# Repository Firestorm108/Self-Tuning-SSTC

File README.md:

# Self-Tuning-SSTC

A solid state Tesla coil that utilizes a half-bridge configuration, automatic tuning through an antenna so that the coil is always in perfect resonance, and a 555-based interrupter. It runs straight off 120VAC with FGA60N65 IGBTs, allowing it to push many many watts. This should make for a good display at Open Sauce 2026.

# Warning

Please do NOT make this under any circumstances unless you are experienced in the field. While this is a solid state coil, it runs off 340VDC from mains and is lethal to anyone who doesn't know what they are doing. I recommened starting with a simple slayer exciter circuit or low voltage primary SSTC circuits. I do not hold any responsibility for what you choose to do with this information.

Demo: https://www.instagram.com/p/DbAHNh3O-ZV/

## Main Features:

 - Integrated 340VDC and 12VDC power supplies
 - 555 Timer Interrupter
 - Antenna feedback
 - Gate drive transformer
 - Half-bridge
 - FGA60N65 based

## Pictures:

# SSTC BOM
*You can find the spreadsheet version here: https://docs.google.com/spreadsheets/d/1Wt0Rxcv9VSmFwRn_iBSPhIluuYkqVSy19_F0Ip-qjvU/edit?usp=sharing

# Bill of Materials (BOM)

## Components

| Item                         | Price | Source  |
| ---------------------------- | ----: | ------- |
| PCB                          |    $5 | JLCPCB  |
| 1N4007                       | $0.76 | DigiKey |
| 10K Potentiometer            | $3.56 | DigiKey |
| Resistor Kit                 |    $5 | Amazon  |
| 470µF 18V Capacitors (×3)    |    $1 | DigiKey |
| 1N4148                       | $0.40 | DigiKey |
| Ceramic Capacitor Kit        |    $7 | Amazon  |
| Ferrite 77                   |    $2 | DigiKey |
| 1N5818                       | $1.50 | DigiKey |
| FGA60N65                     |   $15 | DigiKey |
| Thermistor (30A / 1Ω)        |   $10 | Amazon  |
| L7805                        |    $6 | Amazon  |
| KBPF307G                     |    $1 | DigiKey |
| 0.82µF / 600V Film Capacitor |   $10 | DigiKey |
| KBPC5010W                    |    $4 | DigiKey |
| 1000µF 250V Capacitors (×2)  |   $15 | DigiKey |
| LM555xN                      | $1.50 | DigiKey |
| LM7812 (TO-220)              | $1.80 | DigiKey |
| Screw Terminals              |    $6 | Amazon  |
| 30AWG Magnet Wire            |   $22 | Amazon  |
| 4.5" × 12" PVC Tube          |   $21 | Amazon  |
| Topload                      |   $20 | eBay    |
| Mains Cord                   |    $6 | Amazon  |
| 15mm M3 Standoffs            |    $8 | Amazon  |
| IEC Power Inlet              |    $9 | Amazon  |
| 12VAC Transformer            |   $14 | Amazon  |
| Antenna                      | Owned |         |
| EMI Shielding Tape           |    $7 | Amazon  |
| Rubber Feet                  | Owned |         |
| TO-220 Heatsinks             |    $8 | Amazon  |
| 12AWG Wire                   |   $12 | Amazon  |
| IRFP460                      |   $10 | Amazon  |

---

## Cost Summary

| Vendor  |    Total |
| ------- | -------: |
| DigiKey |  **$80** |
| Amazon  | **$170** |
| eBay    |  **$22** |

### Total Project Cost: **$272**

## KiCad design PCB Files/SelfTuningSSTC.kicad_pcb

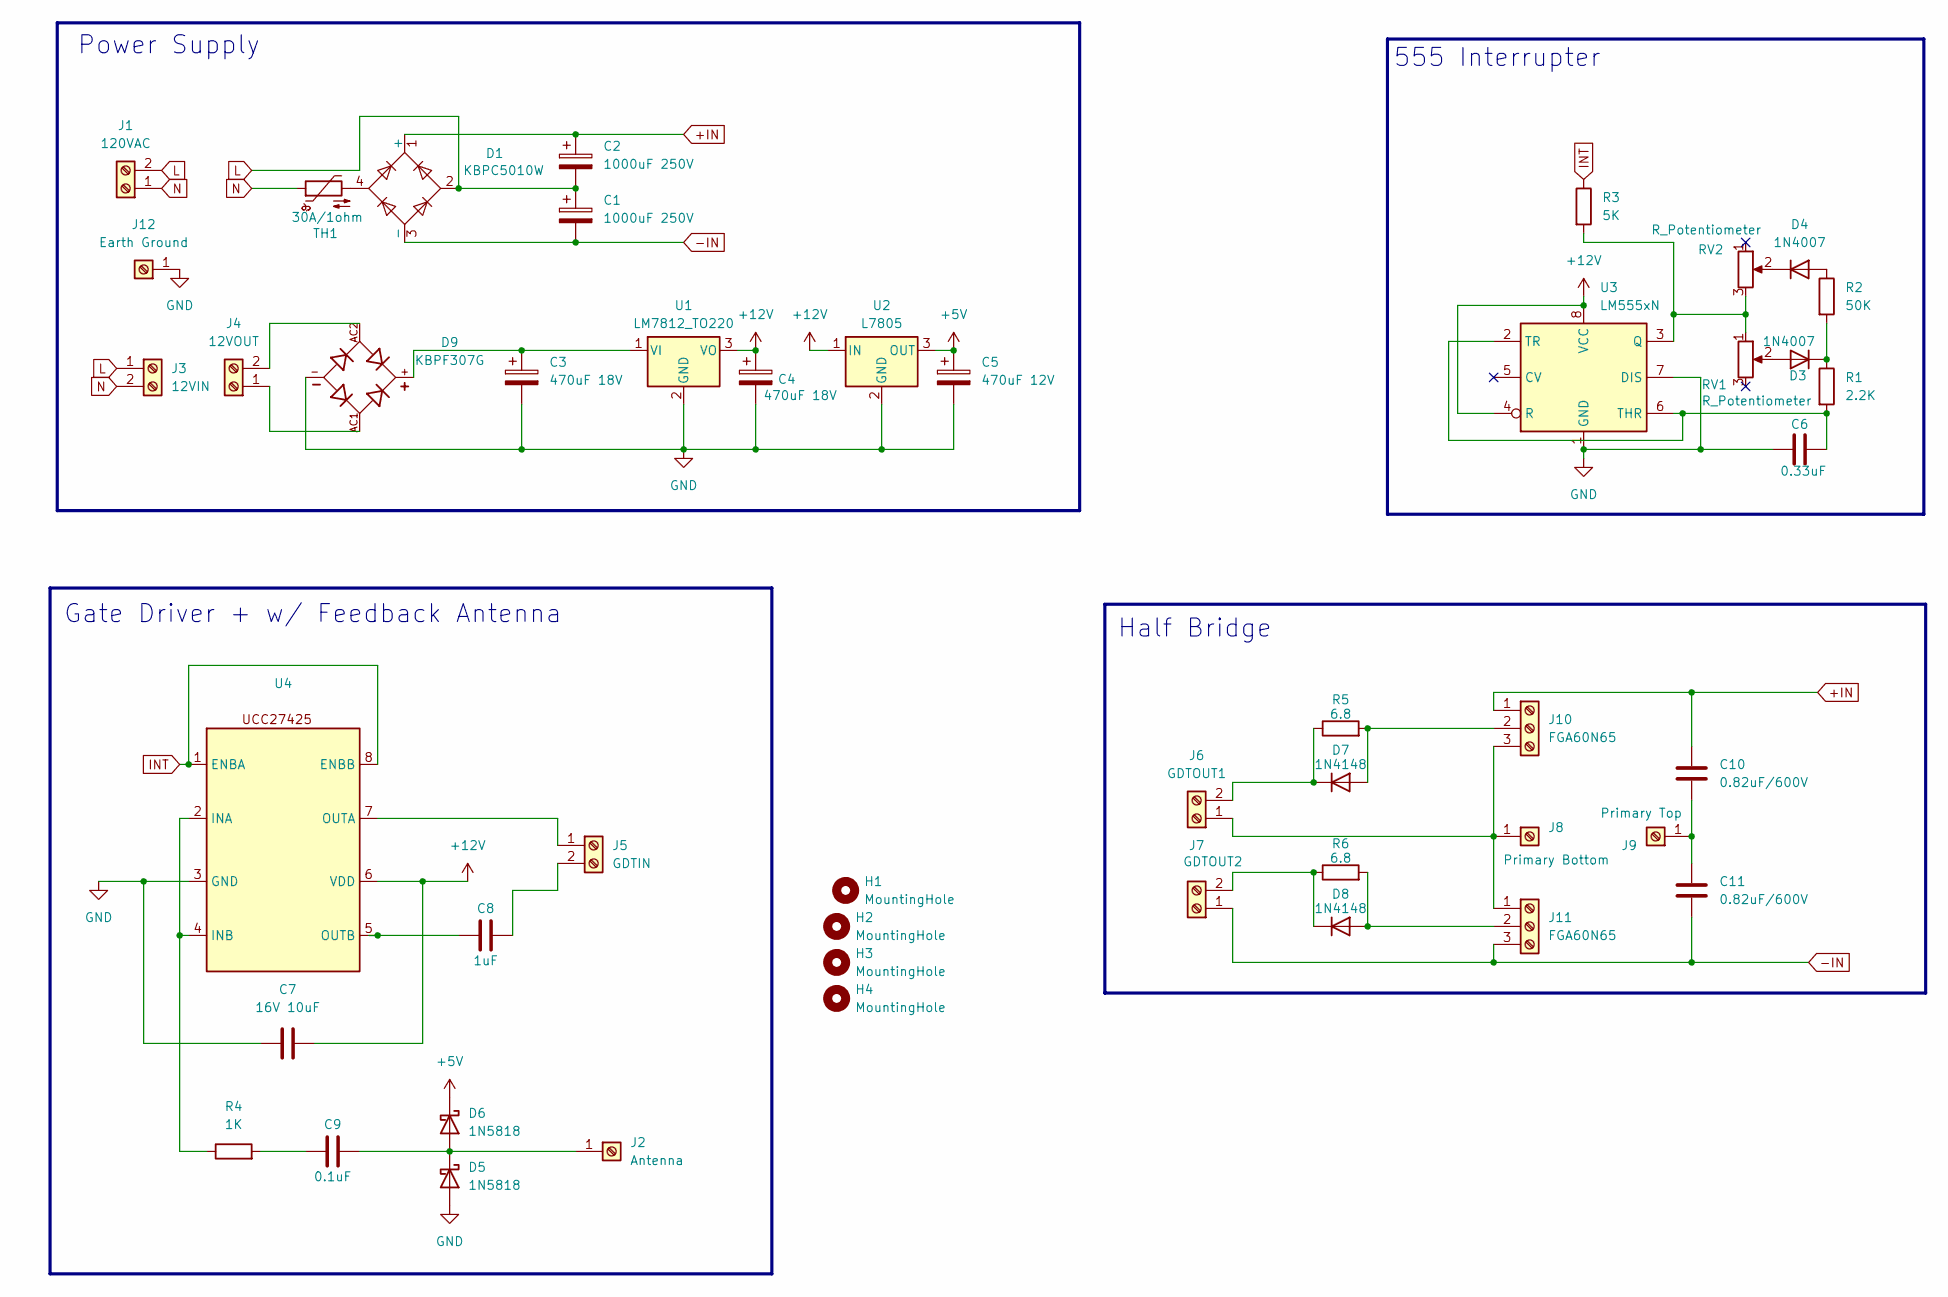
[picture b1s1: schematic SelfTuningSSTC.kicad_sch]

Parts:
C1, C2: 1000uF 250V; CP_Radial_D22.0mm_P10.00mm_SnapIn
C3, C4: 470uF 18V; CP_Radial_D8.0mm_P3.50mm
C5: 470uF 12V; CP_Radial_D8.0mm_P3.50mm
C6: 0.33uF; C_Disc_D5.0mm_W2.5mm_P2.50mm
C7: 16V 10uF; C_Disc_D5.0mm_W2.5mm_P2.50mm
C8: 1uF; C_Disc_D5.0mm_W2.5mm_P2.50mm
C9: 0.1uF; C_Disc_D5.0mm_W2.5mm_P2.50mm
C10, C11: 0.82uF/600V; C_Rect_L31.5mm_W13.0mm_P27.50mm_MKS4
D1: KBPC5010W; Diode_Bridge_GeneSiC_KBPC_W
D3, D4: 1N4007; D_DO-41_SOD81_P10.16mm_Horizontal
D5, D6: 1N5818; D_DO-41_SOD81_P10.16mm_Horizontal
D7, D8: 1N4148; D_DO-35_SOD27_P7.62mm_Horizontal
D9: KBPF307G; SIP350W81P380L1450H1280Q4; PARTREV B2103
H1, H2, H3, H4: MountingHole; MountingHole_3.2mm_M3
J1: 120VAC; PinHeader_1x02_P2.54mm_Vertical
J2: Antenna; PinHeader_1x01_P2.54mm_Vertical
J3: 12VIN; PinHeader_1x02_P2.54mm_Vertical
J4: 12VOUT; PinHeader_1x02_P2.54mm_Vertical
J5: GDTIN; PinHeader_1x02_P2.54mm_Vertical
J6: GDTOUT1; PinHeader_1x02_P2.54mm_Vertical
J7: GDTOUT2; PinHeader_1x02_P2.54mm_Vertical
J8: Primary Bottom; PinHeader_1x01_P2.54mm_Vertical
J9: Primary Top; PinHeader_1x01_P2.54mm_Vertical
J10, J11: FGA60N65; PinHeader_1x03_P2.54mm_Vertical
J12: Earth Ground; PinHeader_1x01_P2.54mm_Vertical
R1: 2.2K; R_Axial_DIN0207_L6.3mm_D2.5mm_P10.16mm_Horizontal
R2: 50K; R_Axial_DIN0207_L6.3mm_D2.5mm_P10.16mm_Horizontal
R3: 5K; R_Axial_DIN0207_L6.3mm_D2.5mm_P10.16mm_Horizontal
R4: 1K; R_Axial_DIN0207_L6.3mm_D2.5mm_P10.16mm_Horizontal
R5, R6: 6.8; R_Axial_DIN0207_L6.3mm_D2.5mm_P10.16mm_Horizontal
RV1, RV2: R_Potentiometer; Potentiometer_Alpha_RD901F-40-00D_Single_Vertical
TH1: 30A/1ohm; RV_Disc_D12mm_W7.9mm_P7.5mm
U1: LM7812_TO220; TO-220-3_Vertical
U2: L7805; TO-220-3_Vertical
U3: LM555xN; DIP-8_W7.62mm
U4: DIP-8_W7.62mm

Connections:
+5V: C5.1, D6.1 (K), U2.3 (OUT)
+12V: C4.1, C7.2, U1.3 (VO), U2.1 (IN), U3.4 (R), U3.8 (VCC), U4.6 (VDD)
+IN: C2.1, C10.1, D1.1 (+), J10.1
-IN: C1.2, C11.2, D1.3 (-), J7.1, J11.3
GND: C3.2, C4.2, C5.2, C6.1, C7.1, D5.2 (A), D9.-, J12.1, U1.2 (GND), U2.2 (GND), U3.1 (GND), U3.7 (DIS), U4.3 (GND)
INT: R3.1, U4.1 (ENBA), U4.8 (ENBB)
L: C1.1, C2.2, D1.2, J1.2, J3.1
N: J1.1, J3.2, TH1.1
unnamed: C9.1, R4.2
unnamed: D1.4, TH1.2
unnamed: D3.2 (A), RV1.2
unnamed: D3.1 (K), R1.1, R2.2
unnamed: D4.2 (A), R2.1
unnamed: D4.1 (K), RV2.2
unnamed: C9.2, D5.1 (K), D6.2 (A), J2.1
unnamed: D7.2 (A), J10.2, R5.2
unnamed: D7.1 (K), J6.2, R5.1
unnamed: D8.2 (A), J11.2, R6.2
unnamed: D8.1 (K), J7.2, R6.1
unnamed: D9.AC1, J4.1
unnamed: D9.AC2, J4.2
unnamed: J5.1, U4.7 (OUTA)
unnamed: C8.2, J5.2
unnamed: C10.2, C11.1, J9.1
unnamed: J6.1, J8.1, J10.3, J11.1
unnamed: C3.1, D9.+, U1.1 (VI)
unnamed: R3.2, RV1.1, RV2.3, U3.3 (Q)
unnamed: C6.2, R1.2, U3.2 (TR), U3.6 (THR)
unnamed: R4.1, U4.2 (INA), U4.4 (INB)
unnamed: C8.1, U4.5 (OUTB)

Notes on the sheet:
Half Bridge
555 Interrupter
Power Supply
Gate Driver + w/ Feedback Antenna

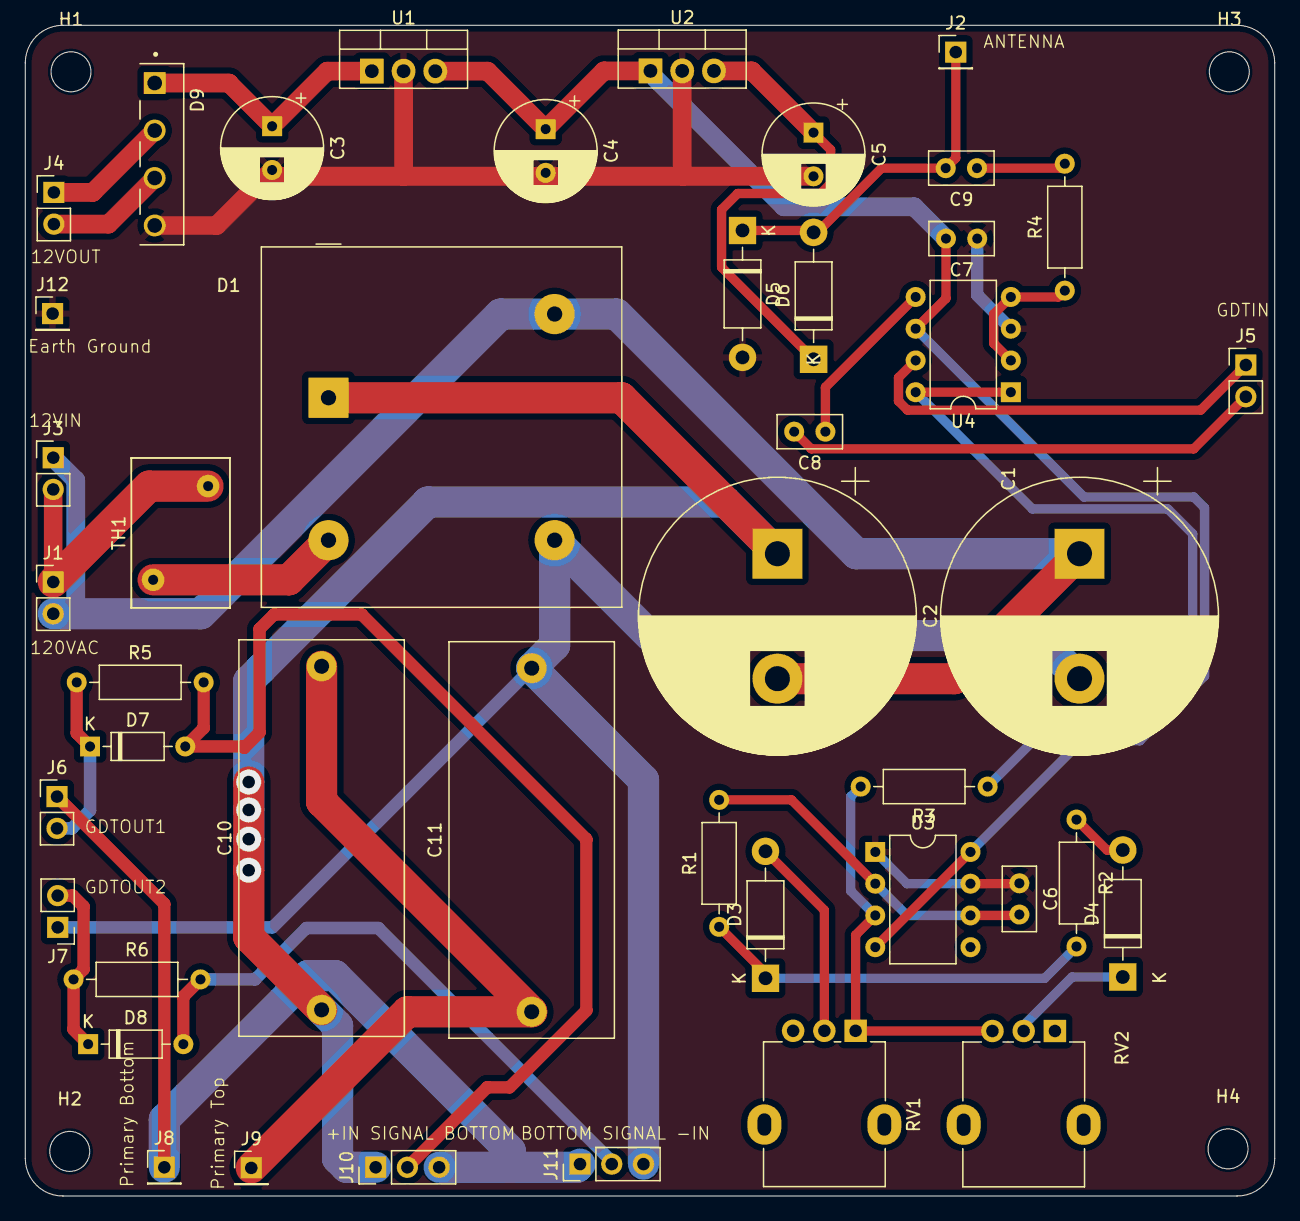
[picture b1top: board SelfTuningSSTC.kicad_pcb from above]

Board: 2 copper layers, 100.0 x 93.7 mm, 48 parts (0 on the bottom side), 30 nets.

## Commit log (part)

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2026-06-21 Add new components to bom.csv
2026-06-21 Fix formatting of main features in README
